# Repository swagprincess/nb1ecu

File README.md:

# A Speeduino Teensy 4.1 ECU For a NB1 Miata #

Integrated Wideband controller (Spartan 3 OEM), MAP and everything needed for it to be PNP.

Using the current fastest Speeduino brain (Teensy 4.1 600MHz).

Config is a modified init.cpp pinmapping case 56 "Bear Cub", adds default pins for features like AC control

Speeduino.ini for TunerStudio is Case 56, changed name to SwagPrincess NB1 PNP

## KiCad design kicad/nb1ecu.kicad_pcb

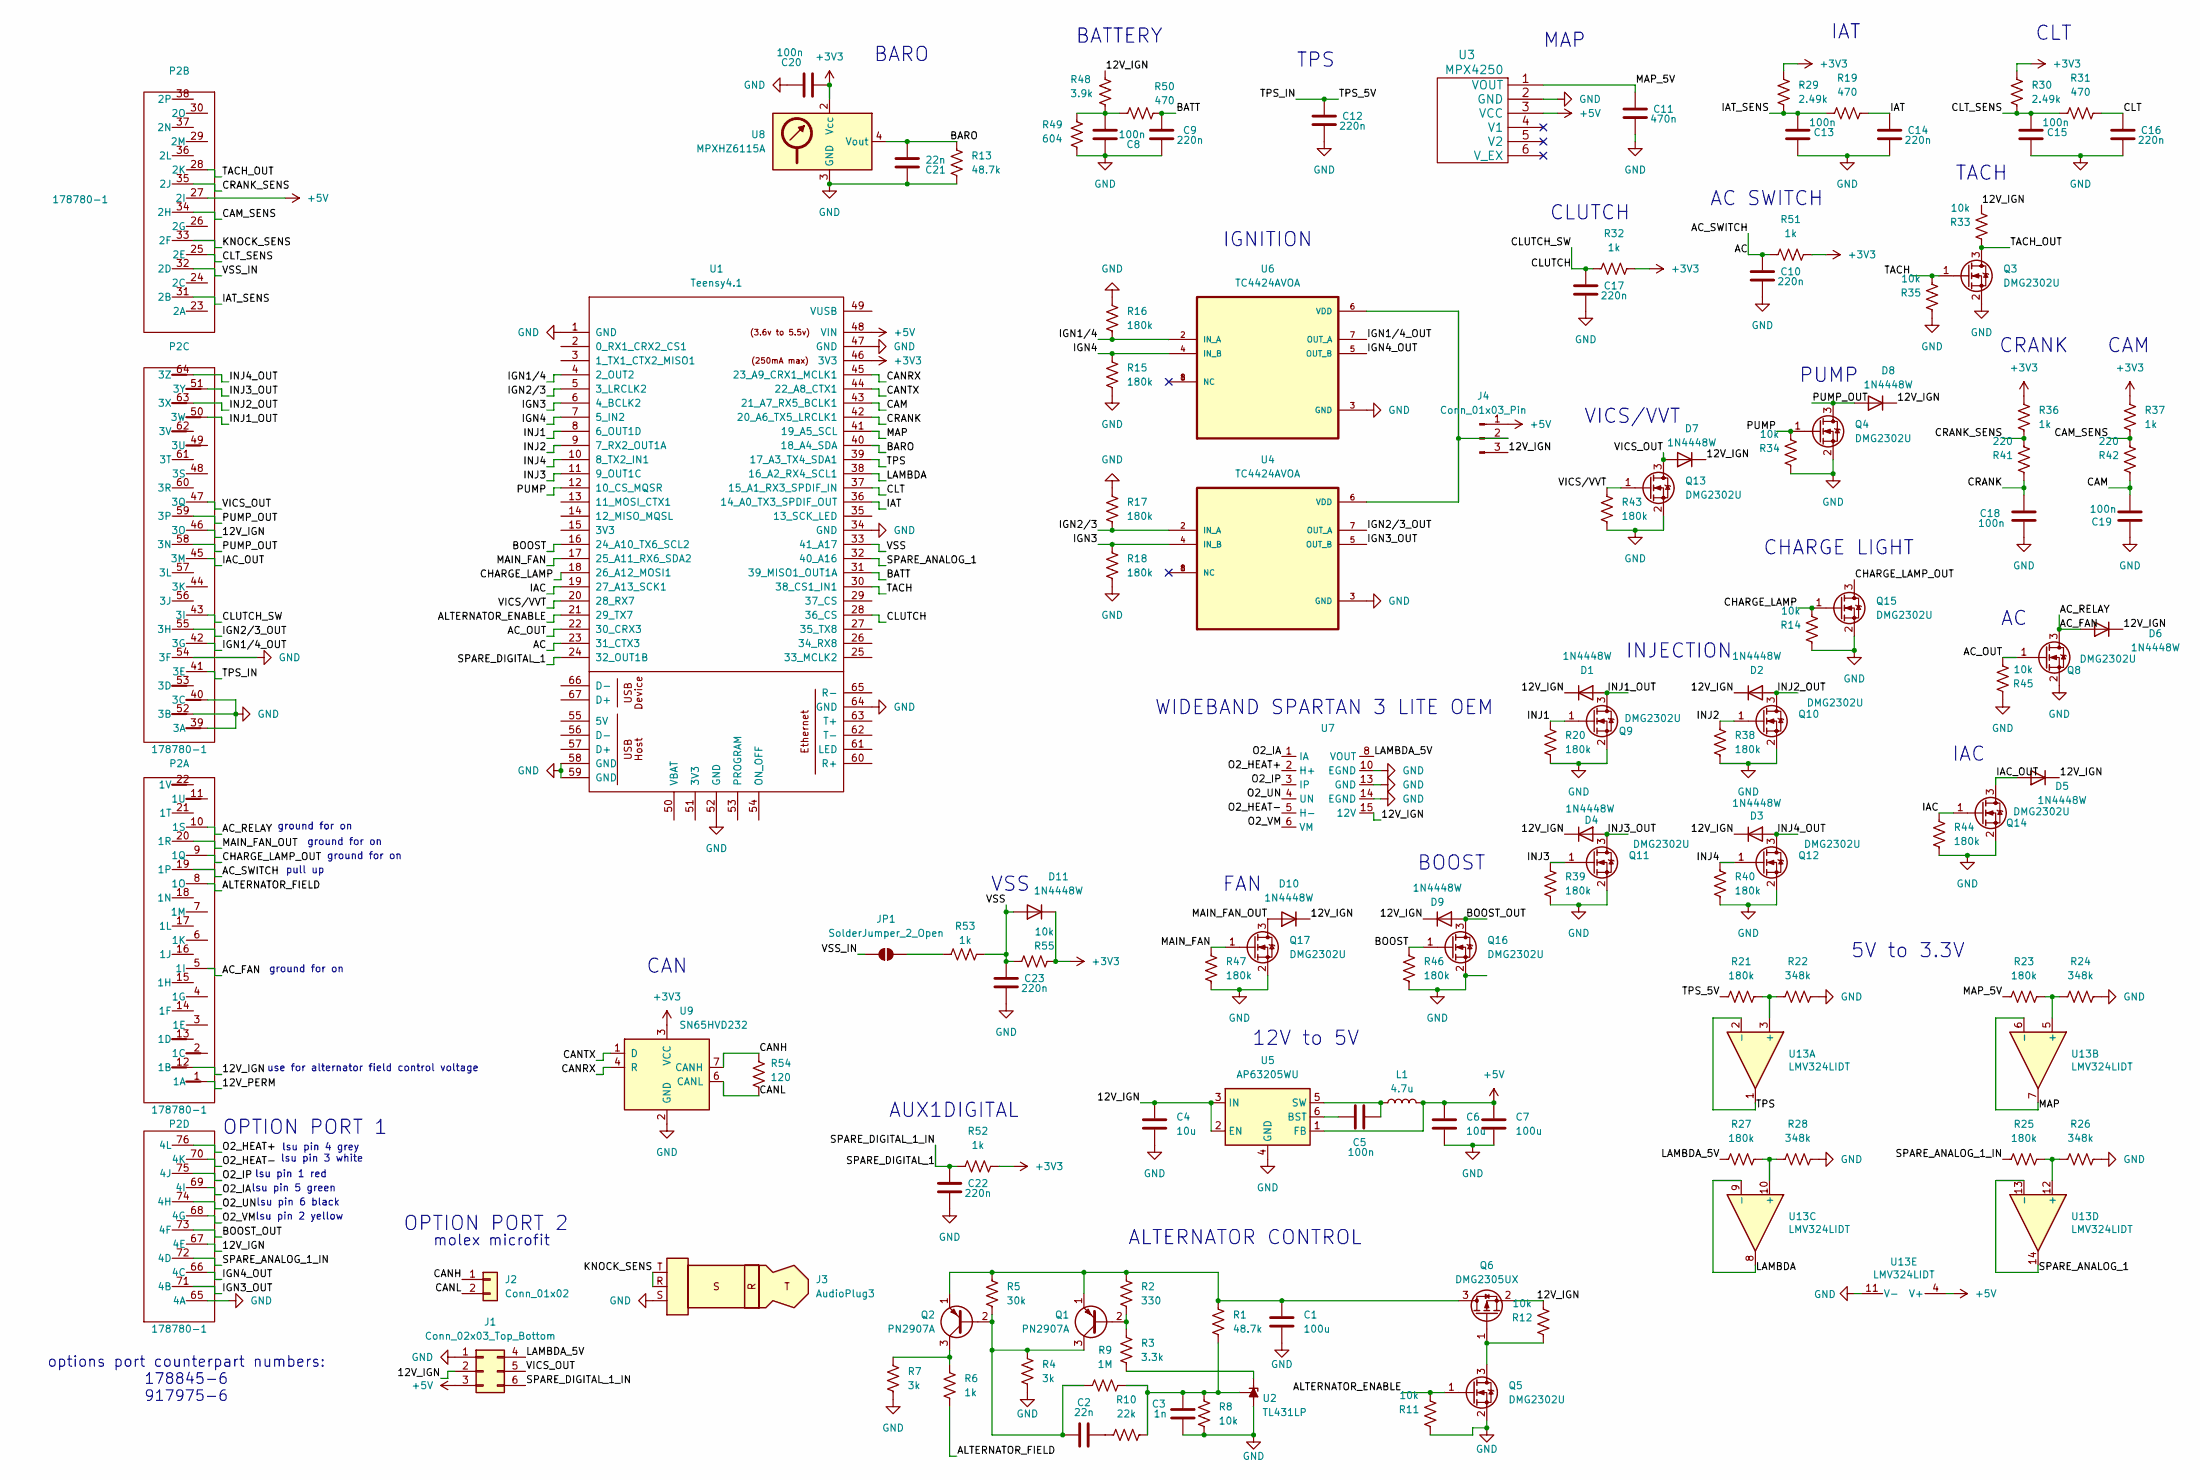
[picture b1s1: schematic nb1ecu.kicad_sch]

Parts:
C1, C7: 100u; CP_Radial_D6.3mm_P2.50mm; LCSC Part # C109392
C2, C21: 22n; C_0805_2012Metric_Pad1.18x1.45mm_HandSolder; LCSC Part # C77069
C3: 1n; C_0805_2012Metric_Pad1.18x1.45mm_HandSolder; LCSC Part # C1791
C4, C6: 10u; C_0805_2012Metric_Pad1.18x1.45mm_HandSolder; LCSC Part # C84416
C5, C8, C13, C15, C18, C19, C20: 100n; C_0805_2012Metric_Pad1.18x1.45mm_HandSolder; LCSC Part # C520083
C9, C10, C12, C14, C16, C17, C22, C23: 220n; C_0805_2012Metric_Pad1.18x1.45mm_HandSolder; LCSC Part # C541527
C11: 470n; C_0805_2012Metric_Pad1.18x1.45mm_HandSolder; LCSC Part # C520079
D1, D2, D3, D4, D5, D6, D7, D8, D9, D10, D11: 1N4448W; D_SOD-123; LCSC Part # C124191
J1: Conn_02x03_Top_Bottom; Molex_Micro-Fit_3.0_43045-0600_2x03_P3.00mm_Horizontal; LCSC Part # C127367
J2: Conn_01x02; Molex_Micro-Fit_3.0_43650-0200_1x02_P3.00mm_Horizontal; LCSC Part # C192562
J3: AudioPlug3; Jack_3.5mm_CUI_SJ1-3525N_Horizontal; LCSC Part # C381120
J4: Conn_01x03_Pin; PinSocket_1x03_P2.54mm_Vertical
JP1: SolderJumper_2_Open; SolderJumper-2_P1.3mm_Open_Pad1.0x1.5mm
L1: 4.7u; L_1008_2520Metric_Pad1.43x2.20mm_HandSolder; LCSC Part # C82314
P2: 178780-1; LCSC Part # C5166246
Q1, Q2: PN2907A; TO-92_Inline_Wide; LCSC Part # C903222
Q3, Q4, Q5, Q8, Q9, Q10, Q11, Q12, Q13, Q14, Q15, Q16, Q17: DMG2302U; SOT-23; LCSC Part # C96613
Q6: DMG2305UX; SOT-23; LCSC Part # C150470
R1, R13: 48.7k; R_0805_2012Metric_Pad1.20x1.40mm_HandSolder; LCSC Part # C865519
R2: 330; R_0805_2012Metric_Pad1.20x1.40mm_HandSolder; LCSC Part # C105878
R3: 3.3k; R_0805_2012Metric_Pad1.20x1.40mm_HandSolder; LCSC Part # C114531
R4, R7: 3k; R_0805_2012Metric_Pad1.20x1.40mm_HandSolder; LCSC Part # C126350
R5: 30k; R_0805_2012Metric_Pad1.20x1.40mm_HandSolder; LCSC Part # C126352
R6, R32, R36, R37, R51, R52, R53: 1k; R_0805_2012Metric_Pad1.20x1.40mm_HandSolder; LCSC Part # C727989
R8, R11, R12, R14, R33, R34, R35, R45, R55: 10k; R_0805_2012Metric_Pad1.20x1.40mm_HandSolder; LCSC Part # C855098
R9: 1M; R_0805_2012Metric_Pad1.20x1.40mm_HandSolder; LCSC Part # C107700
R10: 22k; R_0805_2012Metric_Pad1.20x1.40mm_HandSolder; LCSC Part # C114565
R15, R16, R17, R18, R20, R21, R23, R25, R27, R38, R39, R40, R43, R44, R46, R47: 180k; R_0805_2012Metric_Pad1.20x1.40mm_HandSolder; LCSC Part # C865232
R19, R31, R50: 470; R_0805_2012Metric_Pad1.20x1.40mm_HandSolder; LCSC Part # C114564
R22, R24, R26, R28: 348k; R_0805_2012Metric_Pad1.20x1.40mm_HandSolder; LCSC Part # C228757
R29, R30: 2.49k; R_0805_2012Metric_Pad1.20x1.40mm_HandSolder; LCSC Part # C375522
R41, R42: 220; R_0805_2012Metric_Pad1.20x1.40mm_HandSolder; LCSC Part # C114519
R48: 3.9k; R_0805_2012Metric_Pad1.20x1.40mm_HandSolder; LCSC Part # C865471
R49: 604; R_0805_2012Metric_Pad1.20x1.40mm_HandSolder; LCSC Part # C472205
R54: 120; R_0805_2012Metric_Pad1.20x1.40mm_HandSolder; LCSC Part # C727984
U1: Teensy4.1; Teensy41
U2: TL431LP; TO-92_Inline; LCSC Part # C398376
U3: MPX4250; MPX-4_MAP
U4, U6: TC4424AVOA; SOIC127P599X175-8N; LCSC Part # C44150
U5: AP63205WU; TSOT-23-6; LCSC Part # C2071056
U7: spartan3oem
U8: MPXHZ6115A; SSOP-8_3.95x5.21x3.27mm_P1.27mm; LCSC Part # C3235759
U9: SN65HVD232; SOIC-8_3.9x4.9mm_P1.27mm; LCSC Part # C30530
U13: LMV324LIDT; SOIC-14_3.9x8.7mm_P1.27mm; Manufacturer_Part_Number LMV324LIDT; Digikey Part Number 497-13052-1-ND

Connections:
+3V3: C20.2, D11.1 (K), R29.1, R30.1, R32.2, R36.2, R37.2, R51.2, R52.2, R55.1, U1.46 (3V3), U8.2 (Vcc), U9.3 (VCC)
+5V: C6.1, C7.1, J1.3, J4.1, L1.2, P2.27 (2I), U1.48 (VIN), U3.3 (VCC), U5.1 (FB), U13.4 (V+)
/12V_IGN: C4.1, D1.1 (K), D2.1 (K), D3.1 (K), D4.1 (K), D5.1 (K), D6.1 (K), D7.1 (K), D8.1 (K), D9.1 (K), D10.1 (K), J1.2, J4.3, P2.12 (1B), P2.46 (3O), P2.67 (4E), Q6.2 (S), R12.1, R33.1, R48.2, U5.2 (EN), U5.3 (IN), U7.15 (12V)
/12V_PERM: P2.1 (1A)
/AC: C10.1, P2.19 (1P), R51.1, U1.23 (31_CTX3)
/AC_FAN: D6.2 (A), P2.5 (1I), P2.10 (1S), Q8.3 (D)
/AC_OUT: Q8.1 (G), R45.2, U1.22 (30_CRX3)
/ALTERNATOR_ENABLE: Q5.1 (G), R11.1, U1.21 (29_TX7)
/ALTERNATOR_FIELD: P2.8 (1O), R6.2
/BARO: C21.2, R13.1, U1.40 (18_A4_SDA), U8.4 (Vout)
/BATT: C9.1, R50.1, U1.31 (39_MISO1_OUT1A)
/BOOST: Q16.1 (G), R46.2, U1.16 (24_A10_TX6_SCL2)
/BOOST_OUT: D9.2 (A), P2.73 (4F), Q16.3 (D)
/CAM: C19.2, R42.2, U1.43 (21_A7_RX5_BCLK1)
/CAM_SENS: P2.34 (2H), R37.1, R42.1
/CANH: J2.1, R54.1, U9.7 (CANH)
/CANL: J2.2, R54.2, U9.6 (CANL)
/CANRX: U1.45 (23_A9_CRX1_MCLK1), U9.4 (R)
/CANTX: U1.44 (22_A8_CTX1), U9.1 (D)
/CHARGE_LAMP: Q15.1 (G), R14.1, U1.18 (26_A12_MOSI1)
/CHARGE_LAMP_OUT: P2.9 (1Q), Q15.3 (D)
/CLT: C16.1, R31.1, U1.37 (15_A1_RX3_SPDIF_IN)
/CLT_SENS: C15.1, P2.25 (2E), R30.2, R31.2
/CLUTCH: C17.1, P2.43 (3I), R32.1, U1.28 (36_CS)
/CRANK: C18.2, R41.2, U1.42 (20_A6_TX5_LRCLK1)
/CRANK_SENS: P2.35 (2J), R36.1, R41.1
/IAC: Q14.1 (G), R44.2, U1.19 (27_A13_SCK1)
/IAC_OUT: D5.2 (A), P2.45 (3M), Q14.3 (D)
/IAT: C14.1, R19.1, U1.36 (14_A0_TX3_SPDIF_OUT)
/IAT_SENS: C13.1, P2.31 (2B), R19.2, R29.2
/IGN1/4: R16.1, U1.4 (2_OUT2), U6.2 (IN_A)
/IGN1/4_OUT: P2.42 (3G), U6.7 (OUT_A)
/IGN2/3: R17.1, U1.5 (3_LRCLK2), U4.2 (IN_A)
/IGN2/3_OUT: P2.55 (3H), U4.7 (OUT_A)
/IGN3: R18.2, U1.6 (4_BCLK2), U4.4 (IN_B)
/IGN3_OUT: P2.71 (4B), U4.5 (OUT_B)
/IGN4: R15.2, U1.7 (5_IN2), U6.4 (IN_B)
/IGN4_OUT: P2.66 (4C), U6.5 (OUT_B)
/INJ1: Q9.1 (G), R20.2, U1.8 (6_OUT1D)
/INJ1_OUT: D1.2 (A), P2.50 (3W), Q9.3 (D)
/INJ2: Q10.1 (G), R38.2, U1.9 (7_RX2_OUT1A)
/INJ2_OUT: D2.2 (A), P2.63 (3X), Q10.3 (D)
/INJ3: Q11.1 (G), R39.2, U1.11 (9_OUT1C)
/INJ3_OUT: D4.2 (A), P2.51 (3Y), Q11.3 (D)
/INJ4: Q12.1 (G), R40.2, U1.10 (8_TX2_IN1)
/INJ4_OUT: D3.2 (A), P2.64 (3Z), Q12.3 (D)
/KNOCK_SENS: J3.R, J3.T, P2.33 (2F); also elsewhere on the board
/LAMBDA: U1.38 (16_A2_RX4_SCL1), U13.8, U13.9 (-)
/LAMBDA_5V: J1.4, R27.1, U7.8 (VOUT)
/MAIN_FAN: Q17.1 (G), R47.2, U1.17 (25_A11_RX6_SDA2)
/MAIN_FAN_OUT: D10.2 (A), P2.20 (1R), Q17.3 (D)
/MAP: U1.41 (19_A5_SCL), U13.6 (-), U13.7
/MAP_5V: C11.1, R23.1, U3.1 (VOUT)
/O2_HEAT+: P2.76 (4L), U7.2 (H+)
/O2_HEAT-: P2.70 (4K), U7.5 (H-)
/O2_IA: P2.69 (4I), U7.1 (IA)
/O2_IP: P2.75 (4J), U7.3 (IP)
/O2_UN: P2.74 (4H), U7.4 (UN)
/O2_VM: P2.68 (4G), U7.6 (VM)
/PUMP: Q4.1 (G), R34.1, U1.12 (10_CS_MQSR)
/PUMP_OUT: D8.2 (A), P2.58 (3N), P2.59 (3P), Q4.3 (D)
/SPARE_ANALOG_1: U1.32 (40_A16), U13.13 (-), U13.14
/SPARE_ANALOG_1_IN: P2.72 (4D), R25.1
/SPARE_DIGITAL_1: C22.1, J1.6, R52.1, U1.24 (32_OUT1B)
/TACH: Q3.1 (G), R35.1, U1.30 (38_CS1_IN1)
/TACH_OUT: P2.28 (2K), Q3.3 (D), R33.2
/TPS: U1.39 (17_A3_TX4_SDA1), U13.1, U13.2 (-)
/TPS_5V: C12.1, P2.41 (3E), R21.1
/VICS_OUT: D7.2 (A), J1.5, P2.47 (3Q), Q13.3 (D)
/VICS/VVT: Q13.1 (G), R43.2, U1.20 (28_RX7)
/VSS: C23.1, D11.2 (A), R53.2, R55.2, U1.33 (41_A17)
/VSS_IN: JP1.1 (A), P2.32 (2D)
GND: C1.2, C3.1, C4.2, C6.2, C7.2, C8.2, C9.2, C10.2, C11.2, C12.2, C13.2, C14.2, C15.2, C16.2, C17.2, C18.1, C19.1, C20.1, C21.1, C22.2, C23.2, J1.1, J3.1, J3.S, P2.39 (3A), P2.40 (3C), P2.52 (3B), P2.54 (3F), P2.65 (4A), Q3.2 (S), Q4.2 (S), Q5.2 (S), Q8.2 (S), Q9.2 (S), Q10.2 (S), Q11.2 (S), Q12.2 (S), Q13.2 (S), Q14.2 (S), Q15.2 (S), Q16.2 (S), Q17.2 (S), R4.2, R7.2, R8.2, R11.2, R13.2, R14.2, R15.1, R16.2, R17.2, R18.1, R20.1, R22.2, R24.2, R26.2, R28.2, R34.2, R35.2, R38.1, R39.1, R40.1, R43.1, R44.1, R45.1, R46.1, R47.1, R49.1, U1.1 (GND), U1.34 (GND), U1.47 (GND), U1.52 (GND), U1.58 (GND), U1.59 (GND), U1.64 (GND), U2.2 (A), U3.2 (GND), U4.3 (GND), U5.4 (GND), U6.3 (GND), U7.10 (EGND), U7.13 (GND), U7.14 (EGND), U8.3 (GND), U9.2 (GND), U13.11 (V-); also elsewhere on the board
unnamed: C2.2, R10.1
unnamed: C8.1, R48.1, R49.2, R50.2
unnamed: J4.2, U4.6 (VDD), U6.6 (VDD)
unnamed: JP1.2 (B), R53.1
unnamed: Q1.2 (B), R2.2, R3.1
unnamed: C2.1, Q1.3 (C), Q2.2 (B), R4.1, R5.2, R9.1
unnamed: C1.1, Q1.1 (E), Q2.1 (E), Q6.3 (D), R1.1, R2.1, R5.1
unnamed: Q2.3 (C), R6.1, R7.1
unnamed: Q5.3 (D), Q6.1 (G), R12.2
unnamed: R3.2, U2.3 (K)
unnamed: C3.2, R1.2, R8.1, R9.2, R10.2, U2.1 (REF)
unnamed: C5.2, U5.6 (BST)
unnamed: C5.1, L1.1, U5.5 (SW)
unnamed: R21.2, R22.1, U13.3 (+)
unnamed: R23.2, R24.1, U13.5 (+)
unnamed: R27.2, R28.1, U13.10 (+)
unnamed: R25.2, R26.1, U13.12 (+)

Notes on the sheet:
ground for on
TPS
options port counterpart numbers: 178845-6 917975-6
BATTERY
WIDEBAND SPARTAN 3 LITE OEM
VICS/VVT
CHARGE LIGHT
AUX1DIGITAL
IGNITION
ALTERNATOR CONTROL
IAC
CAM
CLUTCH
VSS
CAN
use for alternator field control voltage
TACH
lsu pin 1 red
lsu pin 3 white
AC SWITCH
OPTION PORT 2
PUMP
lsu pin 4 grey
12V to 5V
lsu pin 2 yellow
BOOST
OPTION PORT 1
MAP
IAT
INJECTION
CRANK
CLT
lsu pin 5 green
5V to 3.3V
BARO
pull up
molex microfit
lsu pin 6 black
FAN

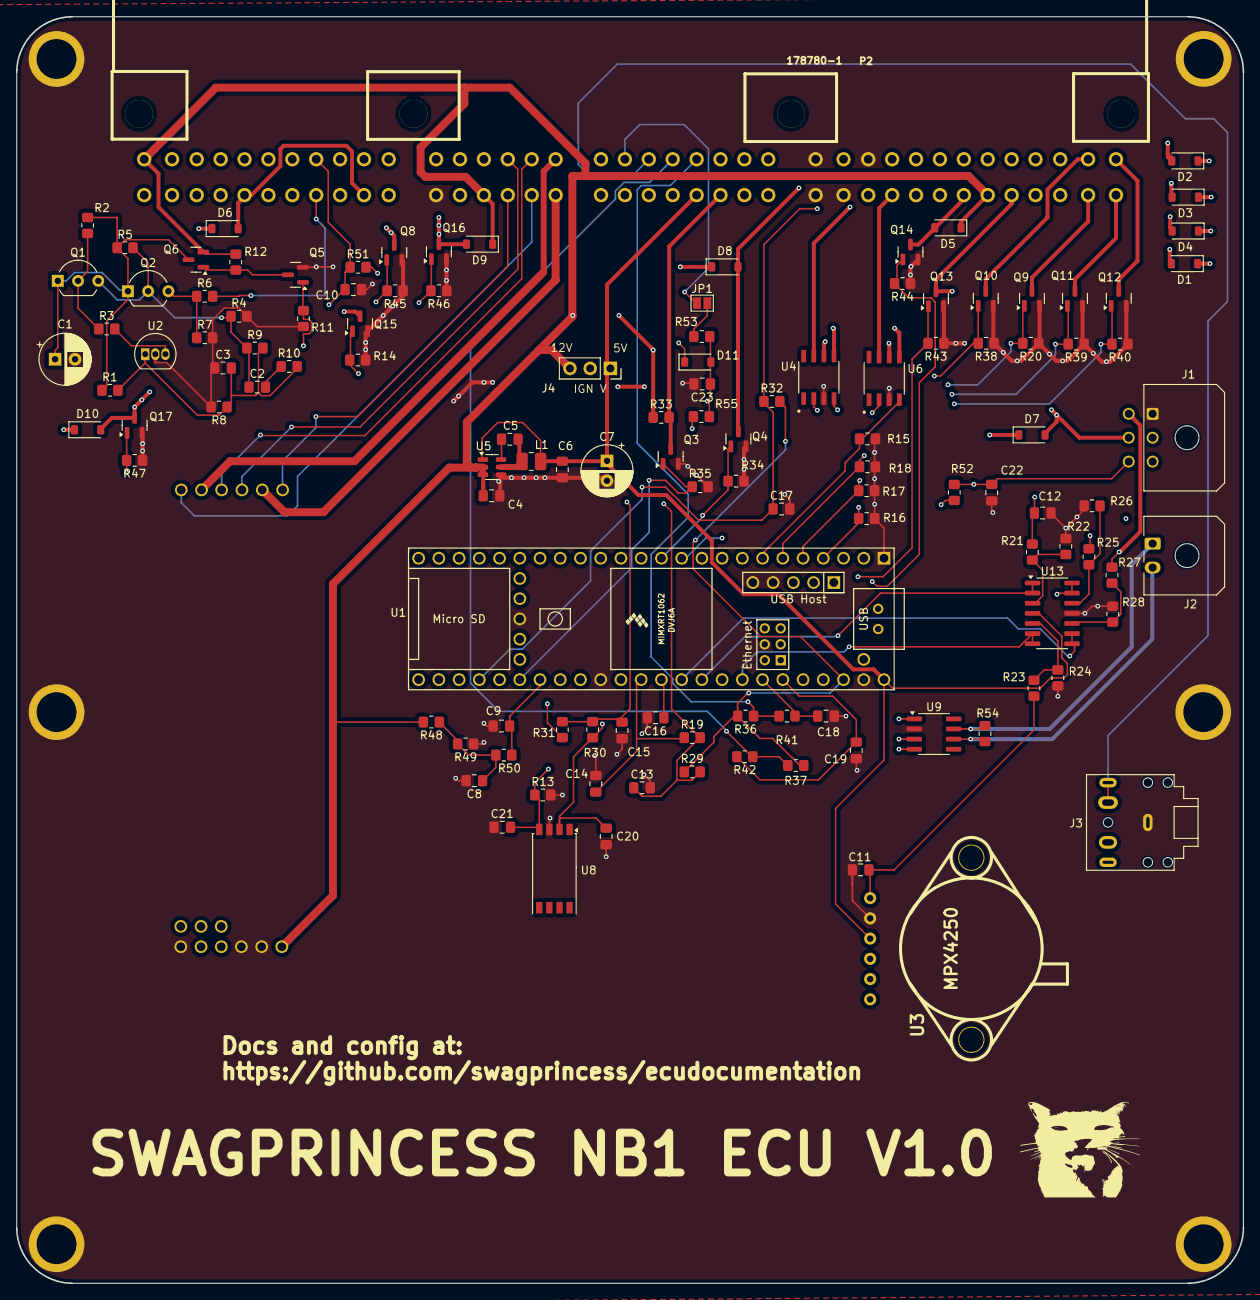
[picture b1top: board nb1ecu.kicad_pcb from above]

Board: 4 copper layers, 154.0 x 159.0 mm, 128 parts (0 on the bottom side), 89 nets.

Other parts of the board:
J1#2, J2#2, J4#2, J5, J6: Conn_01x01; MountingHole_4.5mm_Pad
J3#2: AudioPlug3; Jack_3.5mm_CUI_SJ1-3525N_Horizontal

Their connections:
/KNOCK_SENS: J3#2.R, J3#2.T; also elsewhere on the board
GND: J1#2.1, J2#2.1, J3#2.S, J4#2.1, J5.1, J6.1; also elsewhere on the board

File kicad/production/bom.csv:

Designator,Footprint,Quantity,Value,LCSC Part #
"C1, C7",CP_Radial_D6.3mm_P2.50mm,2,100u,C109392
"C10, C12, C14, C16, C17, C22, C23, C9",0805,8,220n,C541527
C11,0805,1,470n,C520079
"C13, C15, C18, C19, C20, C5, C8",0805,7,100n,C520083
"C2, C21",0805,2,22n,C77069
C3,0805,1,1n,C1791
"C4, C6",0805,2,10u,C84416
"D1, D10, D11, D2, D3, D4, D5, D6, D7, D8, D9",D_SOD-123,11,1N4448W,C124191
J1_2,Molex_Micro-Fit_3.0_43045-0600_2x03_P3.00mm_Horizontal,1,Conn_02x03_Top_Bottom,C127367
J2_2,Molex_Micro-Fit_3.0_43650-0200_1x02_P3.00mm_Horizontal,1,Conn_01x02,C192562
L1,1008,1,4.7u,C82314
P2,178780-1,1,178780-1,C5166246
"Q1, Q2",TO-92_Inline_Wide,2,PN2907A,C513106
"Q10, Q11, Q12, Q13, Q14, Q15, Q16, Q17, Q3, Q4, Q5, Q8, Q9",SOT-23,13,DMG2302U,C96613
Q6,SOT-23,1,DMG2305UX,C150470
"R1, R13",0805,2,48.7k,C865519
R10,0805,1,22k,C114565
"R11, R12, R14, R33, R34, R35, R45, R55, R8",0805,9,10k,C855098
"R15, R16, R17, R18, R20, R21, R23, R25, R27, R38, R39, R40, R43, R44, R46, R47",0805,16,180k,C865232
"R19, R31, R50",0805,3,470,C114564
R2,0805,1,330,C105878
"R22, R24, R26, R28",0805,4,348k,C228757
"R29, R30",0805,2,2.49k,C375522
R3,0805,1,3.3k,C114531
"R32, R36, R37, R51, R52, R53, R6",0805,7,1k,C727989
"R4, R7",0805,2,3k,C126350
"R41, R42",0805,2,220,C114519
R48,0805,1,3.9k,C865471
R49,0805,1,604,C472205
R5,0805,1,30k,C126352
R54,0805,1,120,C727984
R9,0805,1,1M,C107700
U13,SOIC-14_3.9x8.7mm_P1.27mm,1,LMV324LIDT,C262920
U2,TO-92_Inline,1,TL431LP,C398376
"U4, U6",SOIC127P599X175-8N,2,TC4424AVOA,C44150
U5,TSOT-23-6,1,AP63205WU,C2071056
U8,SSOP-8_3.95x5.21x3.27mm_P1.27mm,1,MPXHZ6115A,C3235759
U9,SOIC-8_3.9x4.9mm_P1.27mm,1,SN65HVD232,C30530

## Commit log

2025-08-21 first
2025-09-17 ready to test, need to add part numbers for bom
2025-09-17 add instructions to add pinout
2025-09-17 boost control instead of lambda output on connector and other fixes
2025-09-18 bunch of new features
2025-09-20 options connector
2025-09-29 add CANBUS
2026-01-06 revision
2026-01-07 Official V1.0 milestone, all parts ordered
2026-01-08 add gitattributes
2026-01-08 update gitattributes
2026-01-08 remove gitattributes
2026-05-28 v2 preparation
2026-05-29 fix gitattributes
